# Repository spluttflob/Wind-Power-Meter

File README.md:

# Wind-Power-Meter
Hardware and software for a Raspberry Pi hat which measures the power produced by one or two small wind turbines.

## Hardware
The hardware consists of a circuit board designed in the style of a Raspberry
Pi HAT, but it's not an official HAT because an identifier ROM which is part of
the HAT specification isn't present.  Call it a "Cap" or something. 

The board was designed in the standalone version of Autodesk&trade; Eagle PCB
and the schematic and board files are in the `hardware` directory.

The board uses a pair of Hall-effect current sensors to measure the current
output of the wind turbine; it is expected that the output will be somewhat
dirty DC, and simple filtering is provided.  Voltage dividers reduce the
voltage output of the turbine to safe levels.  Voltage and current are then
digitized with an ADS112C04 analog to digital converter that talks over an
I<sup>2</sup>C interface with the Raspberry Pi. 

## Software
It's just a Python program which gets data from the ADS112C04 and plots some 
plots. 

The software documentation page is at 
<https://spluttflob.github.io/Wind-Power-Meter/>.

### Pi Setup
When setting up a Raspberry Pi, one must enable the I<sup>2</sup>C interface 
using `raspi-setup` or the **Raspberry Pi Configuration** program from the 
desktop's applications menu.  It's often a good idea to enable **SSH**, the 
**VNC** remote desktop, and **SPI** as well. 

This software is designed to run on a "headless" Raspberry Pi. It has been
tested on the October 2021 release of Raspberry Pi OS. 
There's a nice page showing how to set up a "headless" (no monitor) Raspberry
Pi at 
<https://www.tomshardware.com/reviews/raspberry-pi-headless-setup-how-to,6028.html>.

### Dependencies

One needs the **PySimpleGUI** package for plotting as well as **Matplotlib**. 

* To install Matplotlib, run `sudo apt install python3-matplotlib` on the Pi.

* To install PySimpleGUI, run `sudo pip3 install pysimplegui` on the Pi.

* The web application is still being debugged.  It might help to run 
  `sudo pip3 install pysimpleguiweb htmlparser` on the Pi to begin. 

### VNC Issues
The Remmina client on a Linux PC has problems authenticating with the VNC 
desktop server on the Pi unless one adds the line `Authentication=VncAuth` 
to the file `/root/.vnc/config.d/vncserver-x11` on the Pi and then restarts 
the VNC server on the Pi with a command such as 
`systemctl restart vncserver-x11-serviced` (or a reboot). 

Other clients such as those for Windows&trade; or MacOS&trade; may or may not 
require such action to be taken.

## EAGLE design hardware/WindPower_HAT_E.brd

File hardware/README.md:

# Hardware

Here are a schematic and board layout done in standalone Autodesk&trade; Eagle PCB.
They should be easy to import into the Fusion 260&trade; version of Eagle
or into KiCAD (recommended). 

_An image of the schematic for somewhat convenient reference._

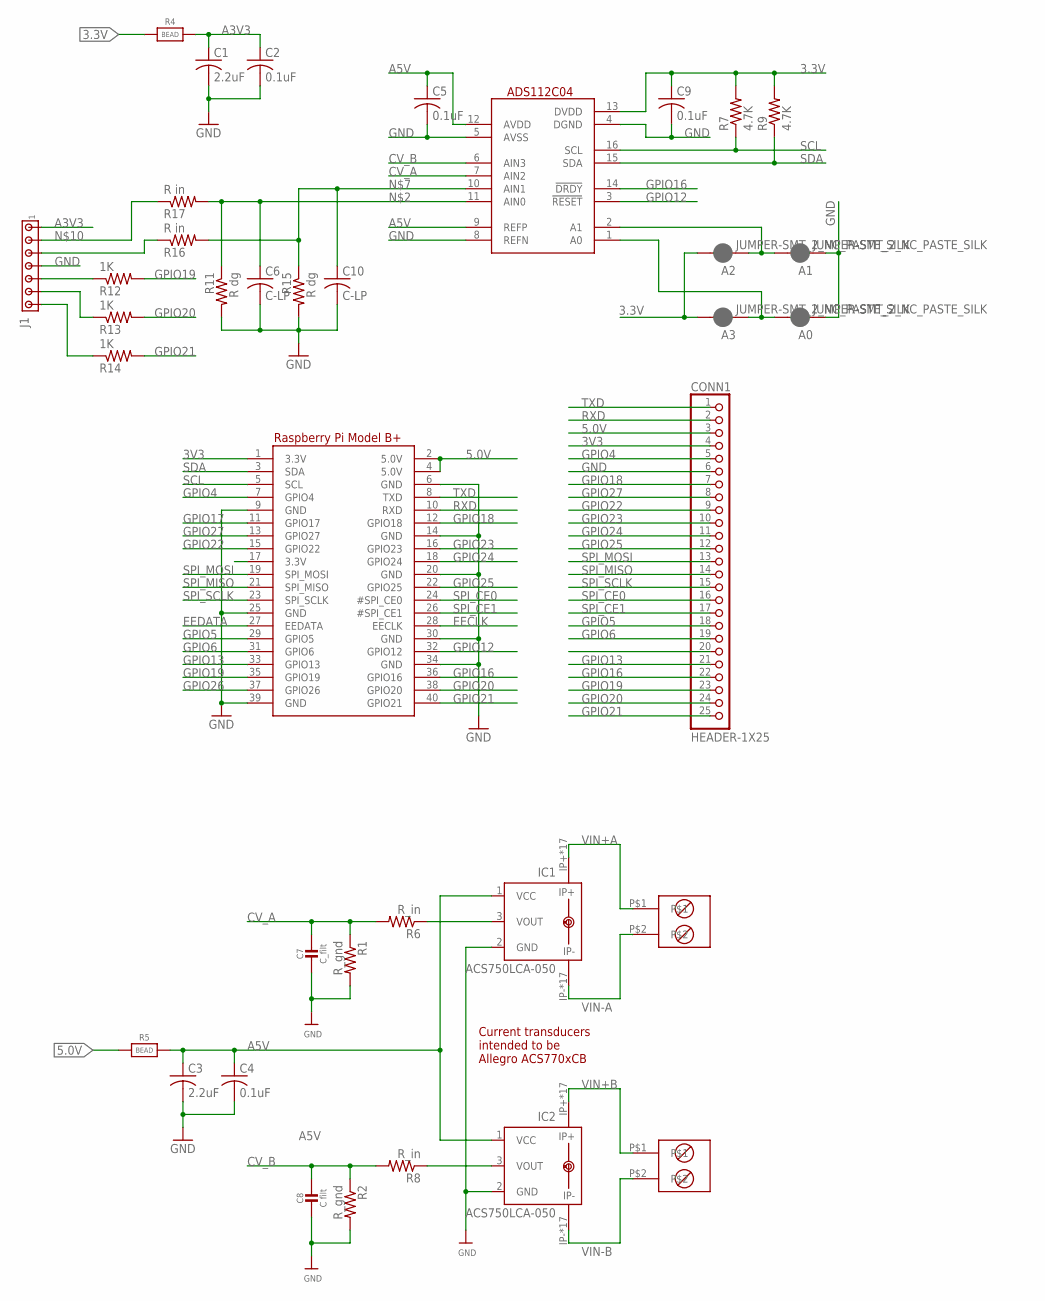
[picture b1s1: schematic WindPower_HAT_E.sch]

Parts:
A0, A1, A2, A3: JUMPER-SMT_2_NC_PASTE_SILK; SMT-JUMPER_2_NC_PASTE_SILK
ADS112C04: ADS112C04TSSOP_FOR_TI_ADC; SOP65P640X120-16N
C1, C3: 2.2uF; C0805
C2, C4, C5, C9: 0.1uF; C0805
C6, C10: C-LP; C0805
C7: C_filt; 0805-NO@1
C8: C filt; 0805-NO@1
CONN1: HEADER-1X25; 1X25_ROUND_70MIL
IC1, IC2: ACS750LCA-050; ACS75050
J1: MTA07-100; 10X07MTA
R1, R2: R_gnd; R0805
R4, R5: BEAD; 0805-NO
R6, R8: R_in; R0805
R7, R9: 4.7K; R0805
R11, R15: R dg; R0805
R12, R13, R14: 1K; R0805
R16, R17: R in; R0805
RPI1: RASPBERRYPI_BPLUS_HATNOSLOTS; PI_HAT_NOSLOTS
U$4, U$5: SCREW-2-6.35MM; SCREWY-2-6.35MM

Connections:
3.3V: A2.2, A3.2, ADS112C04.13 (DVDD), C9.1, R4.1, R7.2, R9.2, RPI1.17 (3.3V)
3V3: CONN1.4, RPI1.1 (3.3V)
5.0V: CONN1.3, R5.1, RPI1.2 (5.0V), RPI1.4 (5.0V)
A3V3: C1.1, C2.1, J1.1, R4.2
A5V: ADS112C04.9 (REFP), ADS112C04.12 (AVDD), C3.1, C4.1, C5.1, IC1.1 (VCC), IC2.1 (VCC), R5.2
CV_A: ADS112C04.7 (AIN2), C7.1, R1.1, R6.2
CV_B: ADS112C04.6 (AIN3), C8.1, R2.1, R8.2
EECLK: RPI1.28 (EECLK)
EEDATA: RPI1.27 (EEDATA)
GND: A0.1, A1.1, ADS112C04.4 (DGND), ADS112C04.5 (AVSS), ADS112C04.8 (REFN), C1.2, C2.2, C3.2, C4.2, C5.2, C6.2, C7.2, C8.2, C9.2, C10.2, CONN1.6, CONN1.20, IC1.2 (GND), IC2.2 (GND), J1.4, R1.2, R2.2, R11.2, R15.2, RPI1.6 (GND), RPI1.9 (GND), RPI1.14 (GND), RPI1.20 (GND), RPI1.25 (GND), RPI1.30 (GND), RPI1.34 (GND), RPI1.39 (GND)
GPIO4: CONN1.5, RPI1.7 (GPIO4)
GPIO5: CONN1.18, RPI1.29 (GPIO5)
GPIO6: CONN1.19, RPI1.31 (GPIO6)
GPIO12: ADS112C04.3 (!RESET), RPI1.32 (GPIO12)
GPIO13: CONN1.21, RPI1.33 (GPIO13)
GPIO16: ADS112C04.14 (!DRDY), CONN1.22, RPI1.36 (GPIO16)
GPIO17: RPI1.11 (GPIO17)
GPIO18: CONN1.7, RPI1.12 (GPIO18)
GPIO19: CONN1.23, R12.2, RPI1.35 (GPIO19)
GPIO20: CONN1.24, R13.2, RPI1.38 (GPIO20)
GPIO21: CONN1.25, R14.2, RPI1.40 (GPIO21)
GPIO22: CONN1.9, RPI1.15 (GPIO22)
GPIO23: CONN1.10, RPI1.16 (GPIO23)
GPIO24: CONN1.11, RPI1.18 (GPIO24)
GPIO25: CONN1.12, RPI1.22 (GPIO25)
GPIO26: RPI1.37 (GPIO26)
GPIO27: CONN1.8, RPI1.13 (GPIO27)
unnamed: IC1.3 (VOUT), R6.1
unnamed: ADS112C04.11 (AIN0), C6.1, R11.1, R17.2
unnamed: IC2.3 (VOUT), R8.1
unnamed: J1.5, R12.1
unnamed: J1.6, R13.1
unnamed: J1.7, R14.1
unnamed: ADS112C04.10 (AIN1), C10.1, R15.1, R16.2
unnamed: A1.2, A2.1, ADS112C04.2 (A1)
unnamed: A0.2, A3.1, ADS112C04.1 (A0)
unnamed: J1.2, R17.1
unnamed: J1.3, R16.1
RXD: CONN1.2, RPI1.10 (RXD)
SCL: ADS112C04.16 (SCL), R7.1, RPI1.5 (SCL)
SDA: ADS112C04.15 (SDA), R9.1, RPI1.3 (SDA)
SPI_CE0: CONN1.16, RPI1.24 (#SPI_CE0)
SPI_CE1: CONN1.17, RPI1.26 (#SPI_CE1)
SPI_MISO: CONN1.14, RPI1.21 (SPI_MISO)
SPI_MOSI: CONN1.13, RPI1.19 (SPI_MOSI)
SPI_SCLK: CONN1.15, RPI1.23 (SPI_SCLK)
TXD: CONN1.1, RPI1.8 (TXD)
VIN+A: IC1.IP+, IC1.IP+@2 (IP+), IC1.IP+@3 (IP+), IC1.IP+@4 (IP+), IC1.IP+@5 (IP+), IC1.IP+@6 (IP+), IC1.IP+@7 (IP+), IC1.IP+@8 (IP+), IC1.IP+@9 (IP+), IC1.IP+@10 (IP+), IC1.IP+@11 (IP+), IC1.IP+@12 (IP+), IC1.IP+@13 (IP+), IC1.IP+@14 (IP+), IC1.IP+@15 (IP+), IC1.IP+@16 (IP+), IC1.IP+@17 (IP+), U$4.P$1
VIN+B: IC2.IP+, IC2.IP+@2 (IP+), IC2.IP+@3 (IP+), IC2.IP+@4 (IP+), IC2.IP+@5 (IP+), IC2.IP+@6 (IP+), IC2.IP+@7 (IP+), IC2.IP+@8 (IP+), IC2.IP+@9 (IP+), IC2.IP+@10 (IP+), IC2.IP+@11 (IP+), IC2.IP+@12 (IP+), IC2.IP+@13 (IP+), IC2.IP+@14 (IP+), IC2.IP+@15 (IP+), IC2.IP+@16 (IP+), IC2.IP+@17 (IP+), U$5.P$1
VIN-A: IC1.IP-, IC1.IP-@2 (IP-), IC1.IP-@3 (IP-), IC1.IP-@4 (IP-), IC1.IP-@5 (IP-), IC1.IP-@6 (IP-), IC1.IP-@7 (IP-), IC1.IP-@8 (IP-), IC1.IP-@9 (IP-), IC1.IP-@10 (IP-), IC1.IP-@11 (IP-), IC1.IP-@12 (IP-), IC1.IP-@13 (IP-), IC1.IP-@14 (IP-), IC1.IP-@15 (IP-), IC1.IP-@16 (IP-), IC1.IP-@17 (IP-), U$4.P$2
VIN-B: IC2.IP-, IC2.IP-@2 (IP-), IC2.IP-@3 (IP-), IC2.IP-@4 (IP-), IC2.IP-@5 (IP-), IC2.IP-@6 (IP-), IC2.IP-@7 (IP-), IC2.IP-@8 (IP-), IC2.IP-@9 (IP-), IC2.IP-@10 (IP-), IC2.IP-@11 (IP-), IC2.IP-@12 (IP-), IC2.IP-@13 (IP-), IC2.IP-@14 (IP-), IC2.IP-@15 (IP-), IC2.IP-@16 (IP-), IC2.IP-@17 (IP-), U$5.P$2

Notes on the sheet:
Current transducers intended to be Allegro ACS770xCB

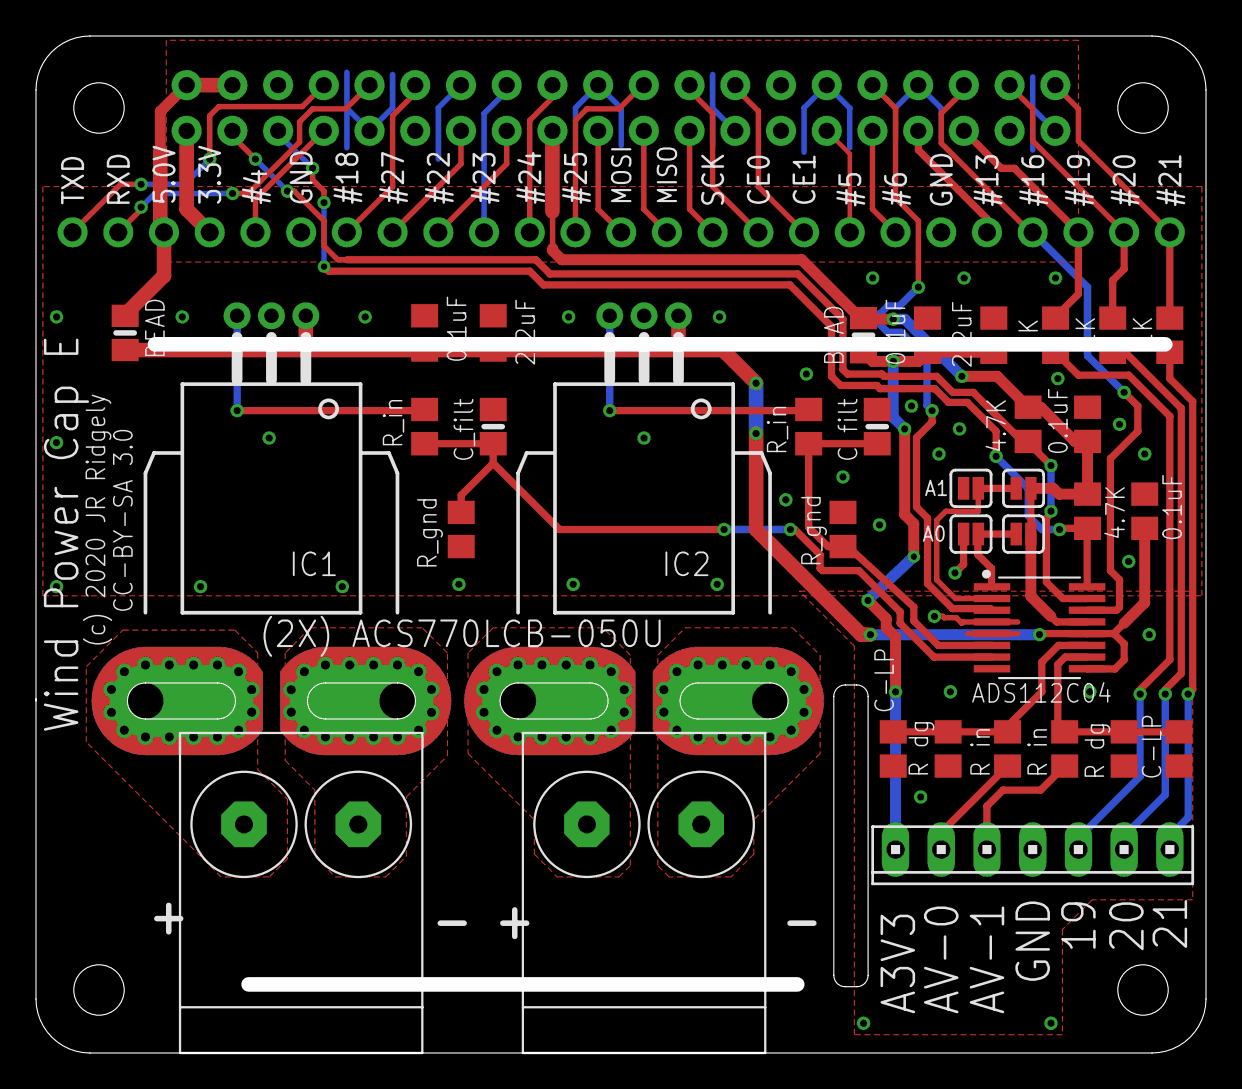
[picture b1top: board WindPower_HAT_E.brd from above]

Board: 2 copper layers, 64.2 x 55.7 mm, 37 parts (0 on the bottom side), 47 nets.

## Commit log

2022-01-09 Organized code, added docs, made a README
2022-01-09 Documentation upgrades
2022-01-09 Fixed readme bugs and added more awesome style
2022-01-09 Images in documentation readme fixed
2022-01-10 Fixed a typo in turbo_hat.py, updated readme
2022-01-10 Fixed a bug in readme which hid the circuit boards
2024-05-17 Added README and image of schematic to hardware section
2024-05-17 Fixed blooper in hardware/README

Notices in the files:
hardware/WindPower_HAT_E.brd:
(c) 2020 JR Ridgely
CC-BY-SA 3.0
parts and their libraries:
microbuilder: This work is placed in the public domain, and may be freely used for commercial and non-commercial work with the following conditions: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
TI-mechatronics: Licensing: Creative Commons ShareAlike 4.0 International - https://creativecommons.org/licenses/by-sa/4.0
